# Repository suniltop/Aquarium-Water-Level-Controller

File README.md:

# Aquarium-Water-Level-Controller

Description

* This circuit designed for espically saltwater aquarium lovers.
* Old school design only through hole package type component is used. Thus handmade soldering is easy for all.
* No MCU, No Firmware :)

PCB picture saved from KiCAD with Raytracing

- Green Led: Everything is fine.
- Yellow Led: Water pump is runnning so, filling aquarium tank or sump tank.
- Red Led: Refill tank is empty.

PCB Picture

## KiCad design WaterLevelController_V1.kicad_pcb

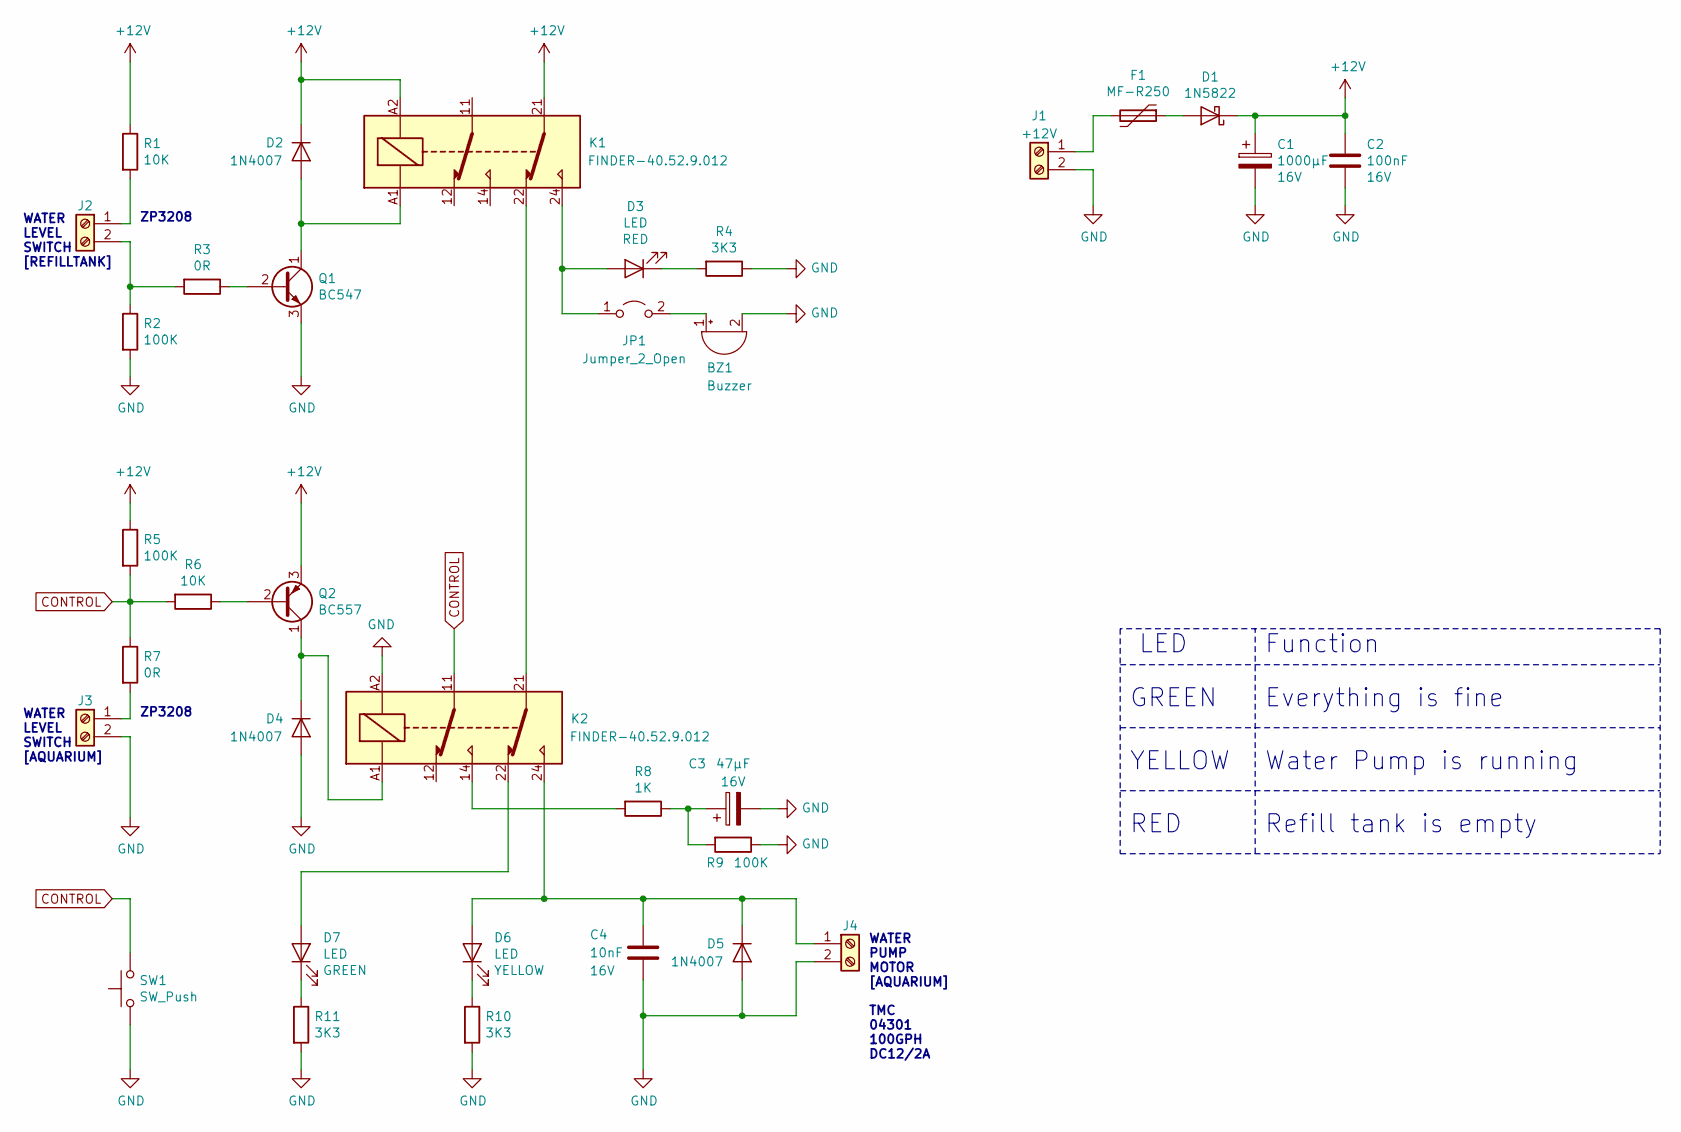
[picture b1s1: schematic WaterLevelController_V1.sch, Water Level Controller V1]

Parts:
BZ1: Buzzer; Buzzer_12x9.5RM7.6
C1: 1000µF; CP_Radial_D10.0mm_P5.00mm; Voltage 16V
C2: 100nF; C_Rect_L7.0mm_W2.5mm_P5.00mm; Voltage 16V
C3: 47µF; CP_Radial_D6.3mm_P2.50mm; Voltage 16V
C4: 10nF; C_Rect_L7.0mm_W2.5mm_P5.00mm; Voltage 16V
D1: 1N5822; D_DO-201AD_P15.24mm_Horizontal
D2, D4, D5: 1N4007; D_DO-35_SOD27_P7.62mm_Horizontal
D3, D6, D7: LED; LED_D3.0mm_FlatTop
F1: MF-R250; Fuse_Bourns_MF-R250
J1, J2, J3, J4: Screw_Terminal_01x02; PhoenixContact_MC-G_02x3.81mm_Angled
JP1: Jumper_2_Open; PinHeader_1x02_P2.54mm_Vertical
K1, K2: FINDER-40.52.9.012; Relay_DPDT_Finder_40.52
Q1: BC547; TO-92_Inline_Wide
Q2: BC557; TO-92_Inline_Wide
R1, R6: 10K; R_Axial_DIN0207_L6.3mm_D2.5mm_P7.62mm_Horizontal
R2, R5, R9: 100K; R_Axial_DIN0207_L6.3mm_D2.5mm_P7.62mm_Horizontal
R3, R7: 0R; R_Axial_DIN0207_L6.3mm_D2.5mm_P7.62mm_Horizontal
R4, R10, R11: 3K3; R_Axial_DIN0207_L6.3mm_D2.5mm_P7.62mm_Horizontal
R8: 1K; R_Axial_DIN0207_L6.3mm_D2.5mm_P7.62mm_Horizontal
SW1: SW_Push; SW_PUSH_6mm

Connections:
+12V: C1.1, C2.1, D1.1 (K), D2.1 (K), K1.21, K1.A2, Q2.3 (E), R1.1, R5.1
CONTROL: K2.11, R5.2, R6.2, R7.1, SW1.2
GND: BZ1.2 (+), C1.2, C2.2, C3.2, C4.2, D4.2 (A), D5.2 (A), J1.2, J3.2, J4.2, K2.A2, Q1.3 (E), R2.2, R4.1, R9.1, R10.2, R11.2, SW1.1
unnamed: BZ1.1 (-), JP1.2 (B)
unnamed: C3.1, R8.1, R9.2
unnamed: C4.1, D5.1 (K), D6.2 (A), J4.1, K2.24
unnamed: D1.2 (A), F1.1
unnamed: D2.2 (A), K1.A1, Q1.1 (C)
unnamed: D3.1 (K), R4.2
unnamed: D3.2 (A), JP1.1 (A), K1.24
unnamed: D4.1 (K), K2.A1, Q2.1 (C)
unnamed: D6.1 (K), R10.1
unnamed: D7.1 (K), R11.1
unnamed: D7.2 (A), K2.22
unnamed: F1.2, J1.1
unnamed: J2.1, R1.2
unnamed: J2.2, R2.1, R3.2
unnamed: J3.1, R7.2
unnamed: K1.22, K2.21
unnamed: K2.14, R8.2
unnamed: Q1.2 (B), R3.1
unnamed: Q2.2 (B), R6.1

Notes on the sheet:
LED
GREEN
YELLOW
RED
WATER LEVEL SWITCH [AQUARIUM]
WATER LEVEL SWITCH [REFILLTANK]
WATER PUMP MOTOR [AQUARIUM]
Water Pump is running
Everything is fine
Refill tank is empty
Function
ZP3208
TMC 04301 100GPH DC12/2A

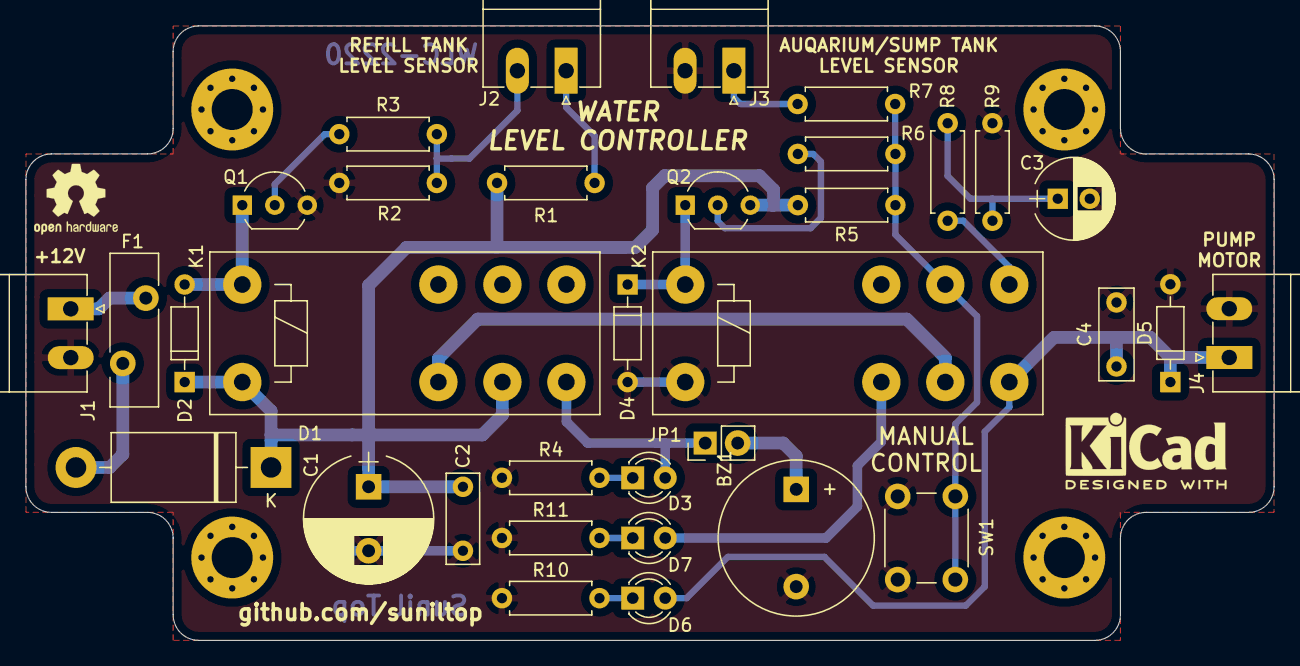
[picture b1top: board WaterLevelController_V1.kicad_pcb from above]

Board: 2 copper layers, 97.5 x 48.0 mm, 34 parts (0 on the bottom side), 22 nets.

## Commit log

2020-05-27 Add files via upload
    Uploaded version WLC-2220 schmatic, pcb, timing diagram files.
2020-05-27 Update README.md
    Adding PCB Picture
2020-05-27 Update README.md
    Led working description has been added.
2020-06-08 Add files via upload
    Added PTC type Resettable Fuse to voltage input
2020-06-08 Add files via upload
    Added gerber files for PCB Production
2020-07-19 Added pcb picture
